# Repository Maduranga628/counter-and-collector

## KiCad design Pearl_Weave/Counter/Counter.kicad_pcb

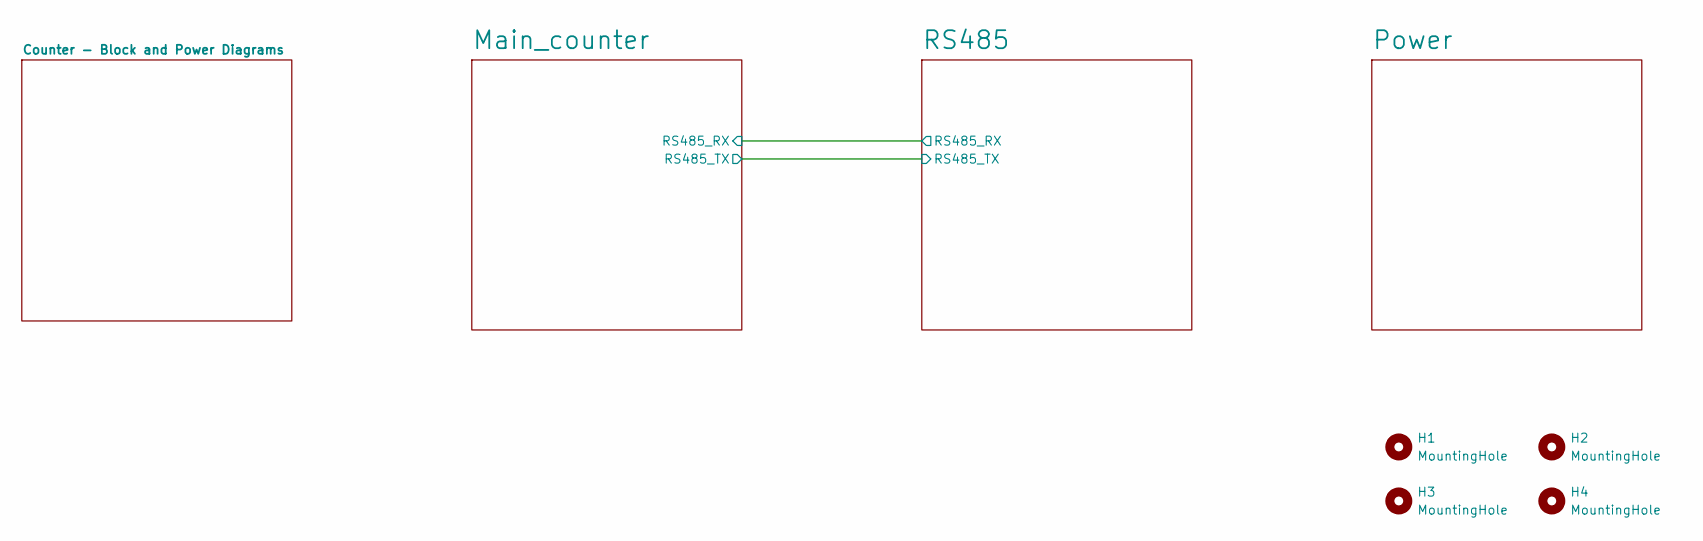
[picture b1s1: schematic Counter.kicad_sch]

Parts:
H1, H2, H3, H4: MountingHole; MountingHole_3.2mm_M3

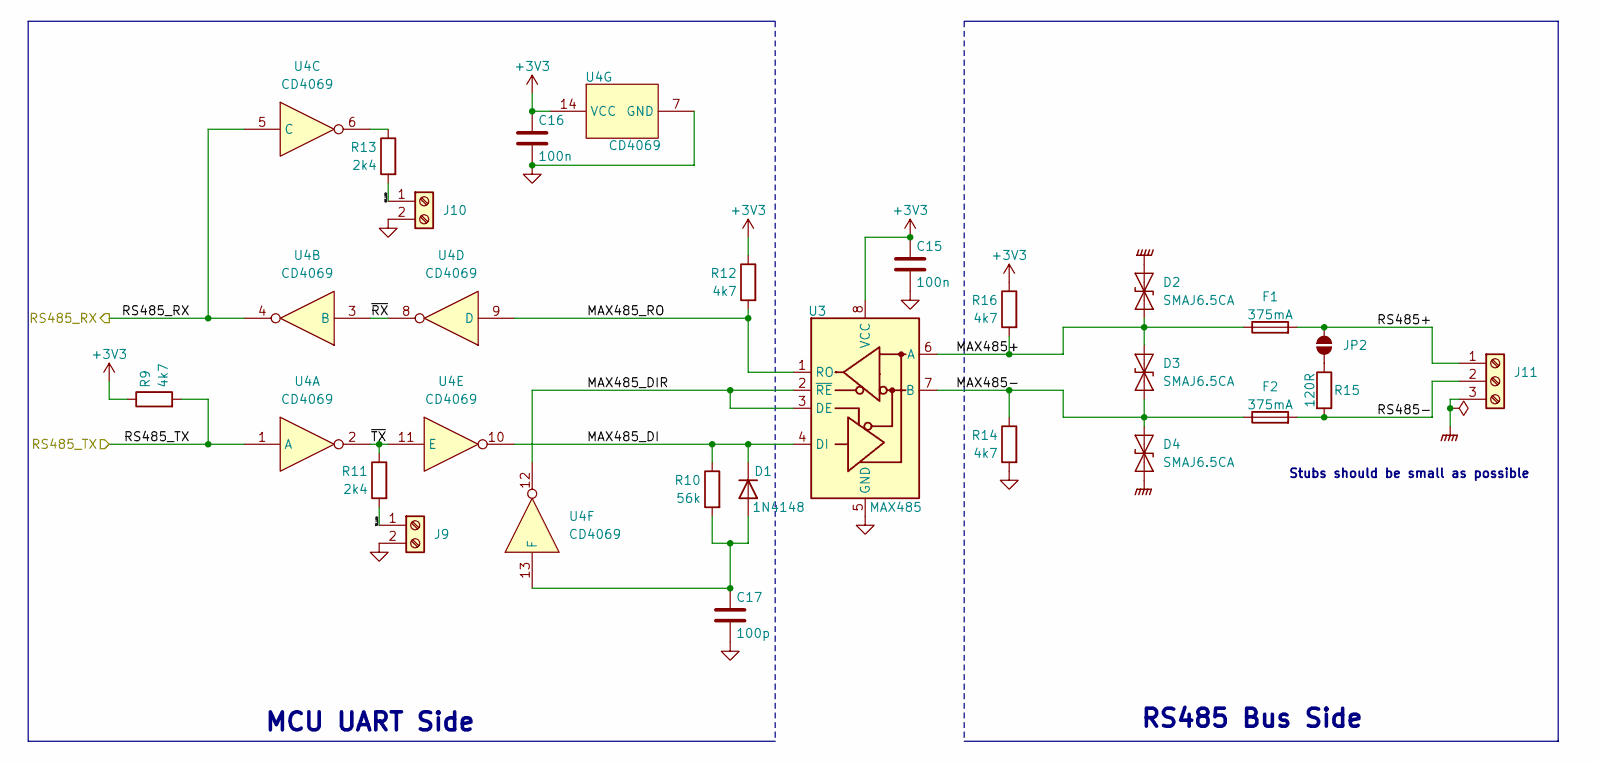
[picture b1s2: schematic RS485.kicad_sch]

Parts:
C15, C16: 100n; C_0603_1608Metric; Manufacturer Part Number CC0603MRX7R7BB104; LCSC Part Number C2172848
C17: 100p; C_0603_1608Metric; Manufacturer Part Number CC0603FRNPO9BN101; LCSC Part Number C513648
D1: 1N4148; D_SOD-523; Manufacturer Part Number 1N4148WT; LCSC Part Number C917006
D2, D3, D4: SMAJ6.5CA; D_SMA; Manufacturer Part Number SMAJ6.5CA; LCSC Part Number C54318614
F1, F2: 375mA; Fuse_1206_3216Metric; Manufacturer Part Number F12F0.375TH; LCSC Part Number C41398705
J9, J10: Screw_Terminal_01x02; TerminalBlock_Phoenix_MPT-0,5-2-2.54_1x02_P2.54mm_Horizontal
J11: Screw_Terminal_01x03; TerminalBlock_Phoenix_MPT-0,5-3-2.54_1x03_P2.54mm_Horizontal
JP2: SolderJumper_2_Open; SolderJumper-2_P1.3mm_Open_RoundedPad1.0x1.5mm
R9, R12, R14, R16: 4k7; R_0603_1608Metric; Manufacturer Part Number RC0603FR-074K7L; LCSC Part Number C99782
R10: 56k; R_0603_1608Metric; Manufacturer Part Number RC0603FR-0756KL; LCSC Part Number C114630
R11, R13: 2k4; R_0603_1608Metric; Manufacturer Part Number RC0603FR-072K4L; LCSC Part Number C114611
R15: 120R; R_0603_1608Metric; Manufacturer Part Number RC0603FR-07120RL; LCSC Part Number C114640
U3: MAX485; SOIC-8_3.9x4.9mm_P1.27mm; Manufacturer Part Number MAX485CSA+T-JSM; LCSC Part Number C18195057
U4: CD4069; SOIC-14_3.9x8.7mm_P1.27mm; Manufacturer Part Number CD4069; LCSC Part Number C3041279

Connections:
+3V3: C15.1, C16.1, R9.1, R12.1, R16.1, U3.8 (VCC), U4.14 (VCC); also elsewhere on the board
/Main_counter/RS485_RX: U4.4, U4.5 (C); also elsewhere on the board
/Main_counter/RS485_TX: R9.2, U4.1 (A); also elsewhere on the board
/RS485/MAX485+: D2.1 (A1), D3.2 (A2), F1.1, R16.2, U3.6 (A)
/RS485/MAX485-: D3.1 (A1), D4.2 (A2), F2.1, R14.1, U3.7 (B)
/RS485/MAX485_DI: D1.1 (K), R10.1, U3.4 (DI), U4.10
/RS485/MAX485_DIR: U3.2 (~RE), U3.3 (DE), U4.12
/RS485/MAX485_RO: R12.2, U3.1 (RO), U4.9 (D)
/RS485/RS485+: F1.2, J11.1, JP2.2 (B)
/RS485/RS485-: F2.2, J11.2, R15.2
/RS485/RX_LED: J10.1, R13.2
/RS485/TX_LED: J9.1, R11.2
/RS485/~RX: U4.3 (B), U4.8
/RS485/~TX: R11.1, U4.2, U4.11 (E)
GND: C15.2, C16.2, C17.2, J9.2, J10.2, R14.2, U3.5 (GND), U4.7 (GND); also elsewhere on the board
GNDPWR: D2.2 (A2), D4.1 (A1), J11.3
unnamed: C17.1, D1.2 (A), R10.2, U4.13 (F)
unnamed: JP2.1 (A), R15.1
unnamed: R13.1, U4.6

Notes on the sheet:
MCU UART Side
Stubs should be small as possible
RS485 Bus Side

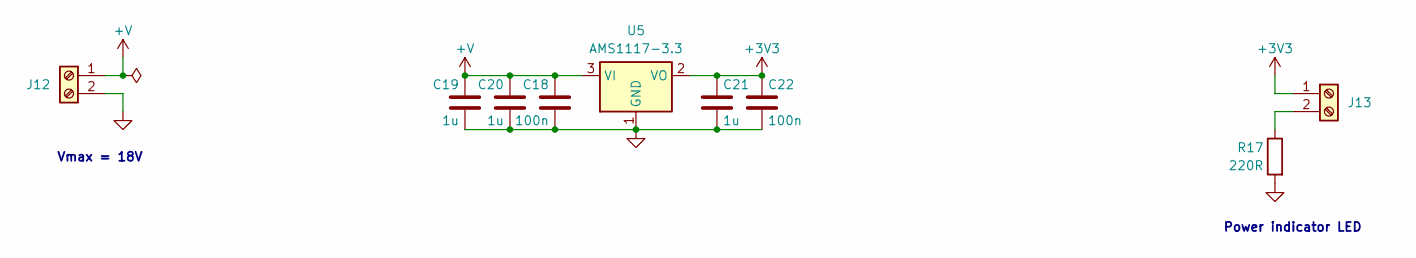
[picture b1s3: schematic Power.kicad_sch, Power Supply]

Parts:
C18, C22: 100n; C_0603_1608Metric; Manufacturer Part Number CC0603MRX7R7BB104; LCSC Part Number C2172848
C19, C20, C21: 1u; C_0603_1608Metric; Manufacturer Part Number CC0603KRX7R9BB105; LCSC Part Number C14664
J12, J13: Screw_Terminal_01x02; TerminalBlock_Phoenix_MPT-0,5-2-2.54_1x02_P2.54mm_Horizontal
R17: 220R; R_0603_1608Metric; Manufacturer Part Number RC0603JR-07220RL; LCSC Part Number C114683
U5: AMS1117-3.3; SOT-223-3_TabPin2; Manufacturer Part Number AMS1117-3.3(SOT-223); LCSC Part Number C5346136

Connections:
+3V3: C21.1, C22.1, J13.1, U5.2 (VO); also elsewhere on the board
+V: C18.1, C19.1, C20.1, J12.1, U5.3 (VI)
GND: C18.2, C19.2, C20.2, C21.2, C22.2, J12.2, R17.2, U5.1 (GND); also elsewhere on the board
unnamed: J13.2, R17.1

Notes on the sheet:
Power indicator LED
Vmax = 18V

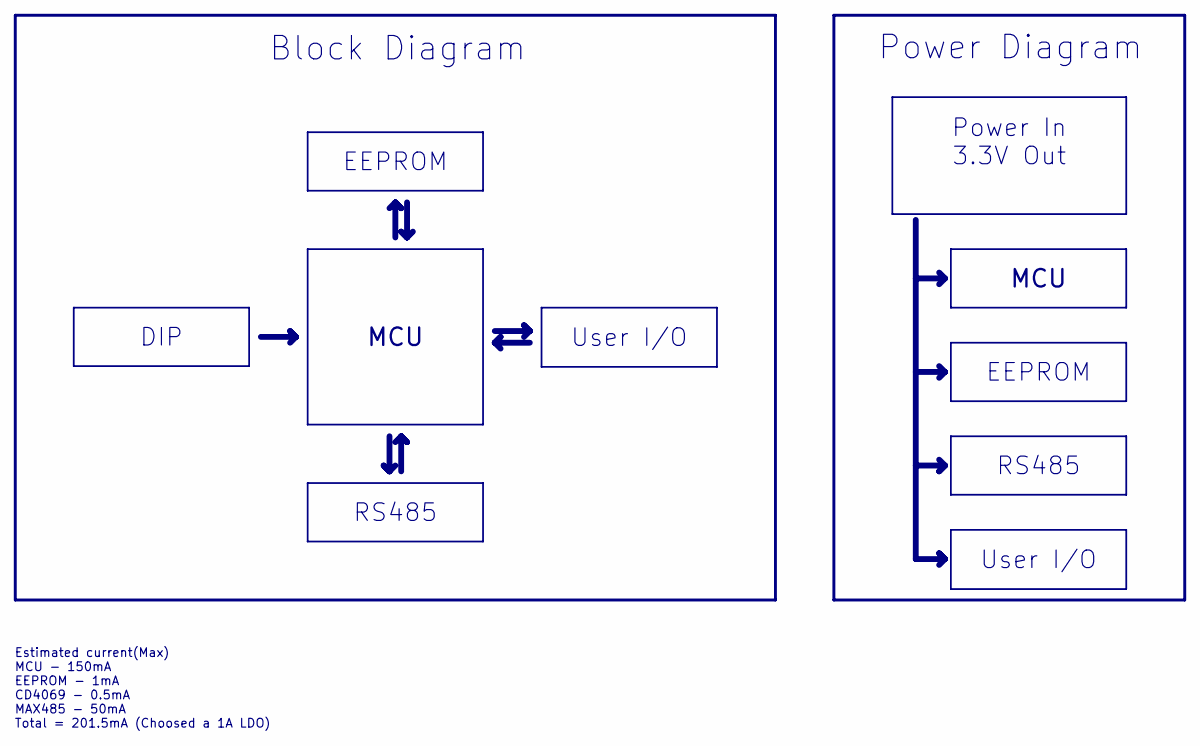
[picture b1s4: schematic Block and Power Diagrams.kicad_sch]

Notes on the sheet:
Block Diagram
Estimated current(Max) MCU - 150mA EEPROM - 1mA CD4069 - 0.5mA MAX485 - 50mA Total = 201.5mA (Choosed a 1A LDO)
Power Diagram
EEPROM
Power In 3.3V Out
MCU
User I/O
RS485
DIP

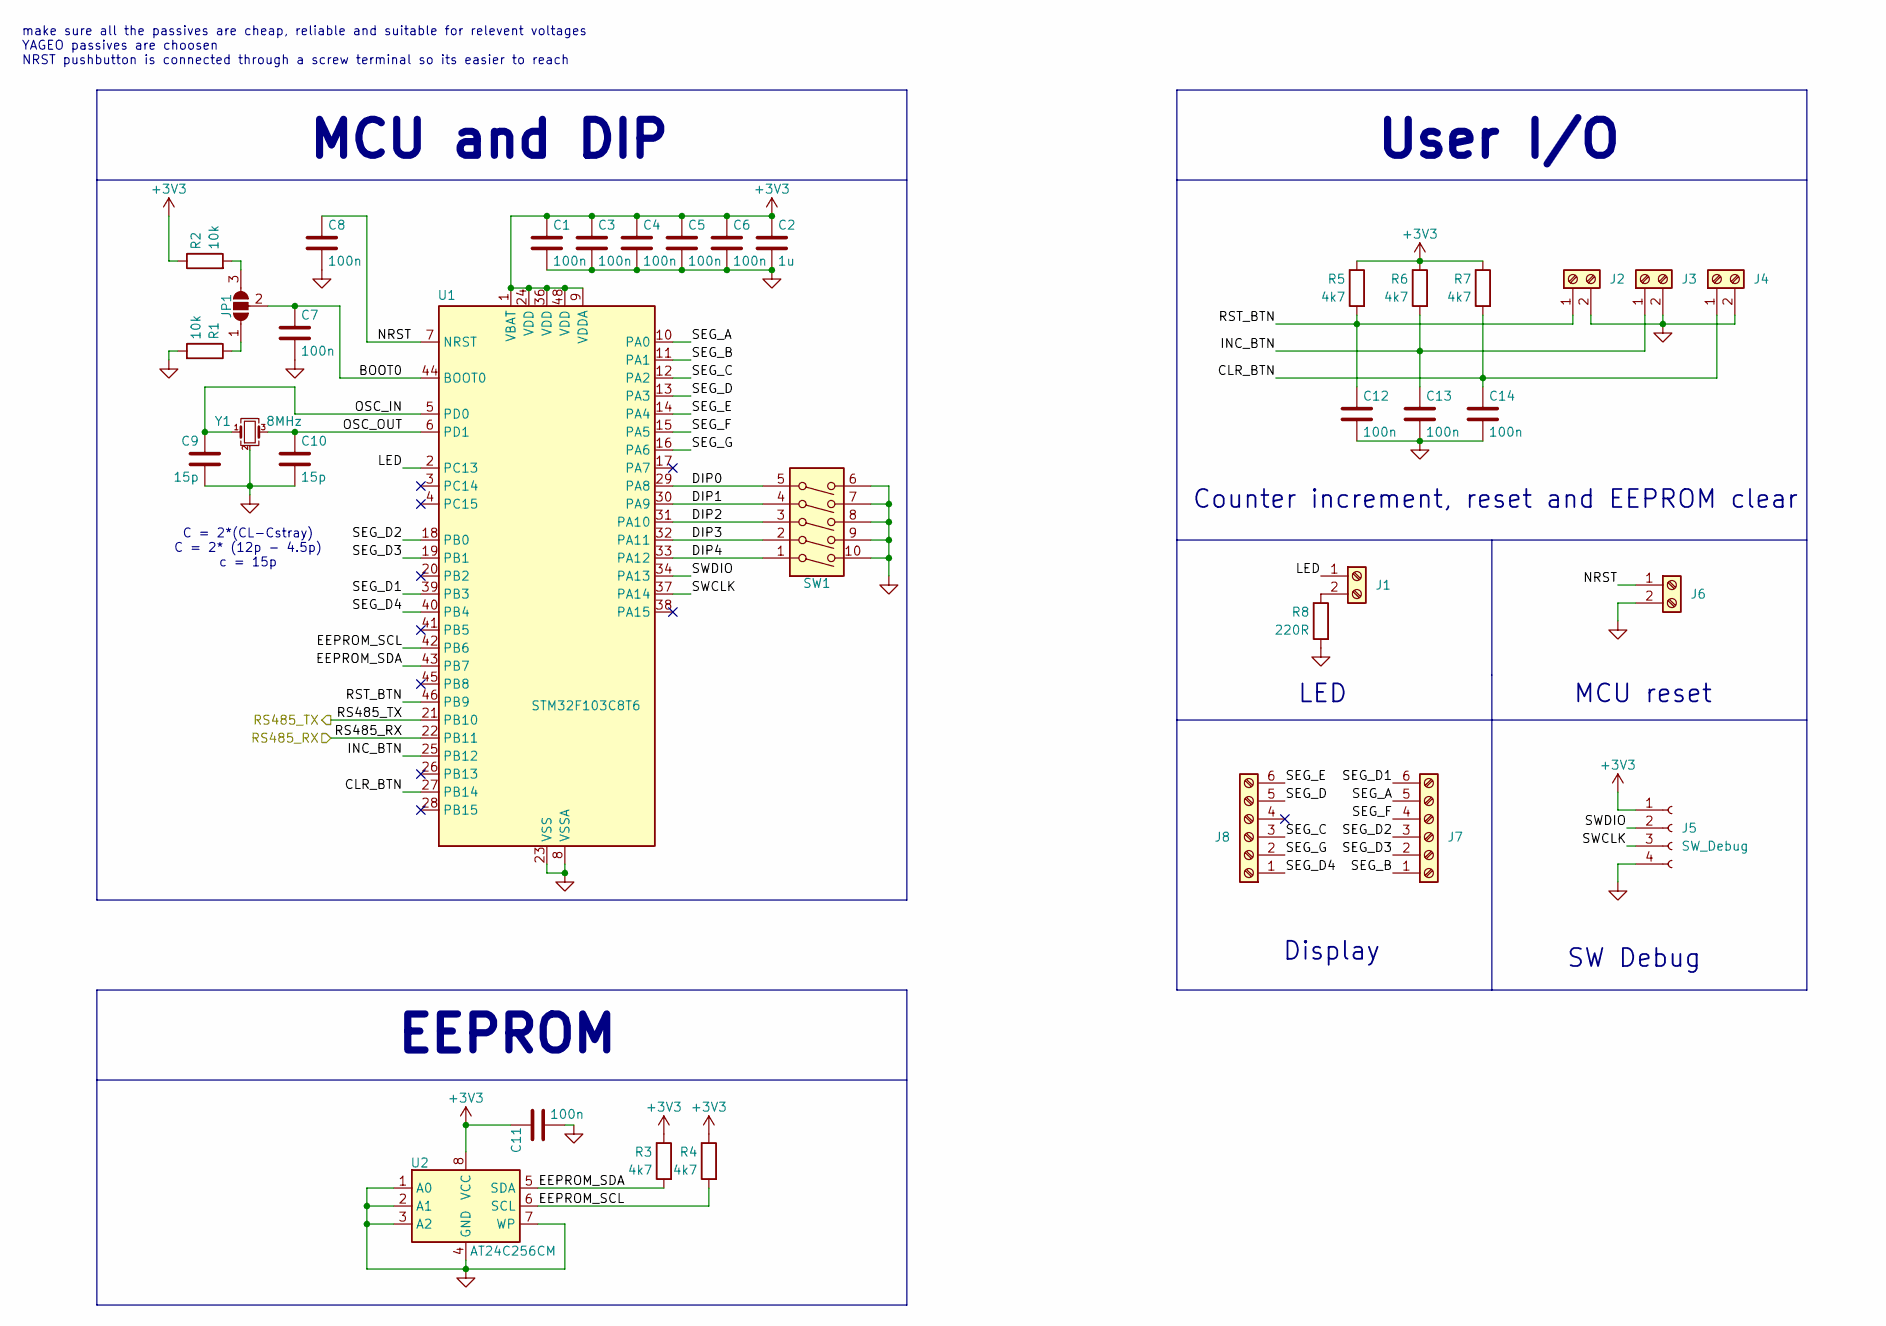
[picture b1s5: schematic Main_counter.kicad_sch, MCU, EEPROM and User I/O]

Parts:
C1, C3, C4, C5, C6, C7, C8, C11, C12, C13, C14: 100n; C_0603_1608Metric; Manufacturer Part Number CC0603MRX7R7BB104; LCSC Part Number C2172848
C2: 1u; C_0603_1608Metric; Manufacturer Part Number CC0603KRX7R9BB105; LCSC Part Number C14664
C9, C10: 15p; C_0603_1608Metric; Manufacturer Part Number CC0603FRNPO9BN150; LCSC Part Number C519483
J1, J2, J3, J4, J6: Screw_Terminal_01x02; TerminalBlock_Phoenix_MPT-0,5-2-2.54_1x02_P2.54mm_Horizontal
J5: SW_Debug; PinSocket_1x04_P2.54mm_Vertical
J7, J8: Screw_Terminal_01x06; TerminalBlock_Phoenix_MPT-0,5-6-2.54_1x06_P2.54mm_Horizontal
JP1: SolderJumper_3_Open; SolderJumper-3_P1.3mm_Open_RoundedPad1.0x1.5mm
R1, R2: 10k; R_0603_1608Metric; Manufacturer Part Number RC0603JR-0710KL; LCSC Part Number C99198
R3, R4, R5, R6, R7: 4k7; R_0603_1608Metric; Manufacturer Part Number RC0603FR-074K7L; LCSC Part Number C99782
R8: 220R; R_0603_1608Metric; Manufacturer Part Number RC0603JR-07220RL; LCSC Part Number C114683
SW1: SW_DIP_x05; SW_DIP_SPSTx05_Slide_9.78x14.88mm_W7.62mm_P2.54mm
U1: STM32F103C8T6; LQFP-48_7x7mm_P0.5mm
U2: AT24C256CM; SOP-8_3.76x4.96mm_P1.27mm; Manufacturer Part Number AT24C256CM/TR; LCSC Part Number C7432367
Y1: 8MHz; Crystal_SMD_3225-4Pin_3.2x2.5mm; Manufacturer Part Number SX32Y008000BC1T001; LCSC Part Number C20617233

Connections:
+3V3: C1.1, C2.1, C3.1, C4.1, C5.1, C6.1, C11.1, J5.1, R2.1, R3.1, R4.1, R5.1, R6.1, R7.1, U1.1 (VBAT), U1.9 (VDDA), U1.24 (VDD), U1.36 (VDD), U1.48 (VDD), U2.8 (VCC); also elsewhere on the board
/Main_counter/BOOT0: C7.1, JP1.2 (C), U1.44 (BOOT0)
/Main_counter/CLR_BTN: C14.1, J4.1, R7.2, U1.27 (PB14)
/Main_counter/DIP0: SW1.5, U1.29 (PA8)
/Main_counter/DIP1: SW1.4, U1.30 (PA9)
/Main_counter/DIP2: SW1.3, U1.31 (PA10)
/Main_counter/DIP3: SW1.2, U1.32 (PA11)
/Main_counter/DIP4: SW1.1, U1.33 (PA12)
/Main_counter/EEPROM_SCL: R4.2, U1.42 (PB6), U2.6 (SCL)
/Main_counter/EEPROM_SDA: R3.2, U1.43 (PB7), U2.5 (SDA)
/Main_counter/INC_BTN: C13.1, J3.1, R6.2, U1.25 (PB12)
/Main_counter/LED: J1.1, U1.2 (PC13)
/Main_counter/NRST: C8.1, J6.1, U1.7 (NRST)
/Main_counter/OSC_IN: C9.1, U1.5 (PD0), Y1.1
/Main_counter/OSC_OUT: C10.1, U1.6 (PD1), Y1.3
/Main_counter/RS485_RX: U1.22 (PB11); also elsewhere on the board
/Main_counter/RS485_TX: U1.21 (PB10); also elsewhere on the board
/Main_counter/RST_BTN: C12.1, J2.1, R5.2, U1.46 (PB9)
/Main_counter/SEG_A: J7.5, U1.10 (PA0)
/Main_counter/SEG_B: J7.1, U1.11 (PA1)
/Main_counter/SEG_C: J8.3, U1.12 (PA2)
/Main_counter/SEG_D: J8.5, U1.13 (PA3)
/Main_counter/SEG_D1: J7.6, U1.39 (PB3)
/Main_counter/SEG_D2: J7.3, U1.18 (PB0)
/Main_counter/SEG_D3: J7.2, U1.19 (PB1)
/Main_counter/SEG_D4: J8.1, U1.40 (PB4)
/Main_counter/SEG_E: J8.6, U1.14 (PA4)
/Main_counter/SEG_F: J7.4, U1.15 (PA5)
/Main_counter/SEG_G: J8.2, U1.16 (PA6)
/Main_counter/SWCLK: J5.3, U1.37 (PA14)
/Main_counter/SWDIO: J5.2, U1.34 (PA13)
GND: C1.2, C2.2, C3.2, C4.2, C5.2, C6.2, C7.2, C8.2, C9.2, C10.2, C11.2, C12.2, C13.2, C14.2, J2.2, J3.2, J4.2, J5.4, J6.2, R1.2, R8.2, SW1.6, SW1.7, SW1.8, SW1.9, SW1.10, U1.8 (VSSA), U1.23 (VSS), U1.35 (VSS), U1.47 (VSS), U2.1 (A0), U2.2 (A1), U2.3 (A2), U2.4 (GND), U2.7 (WP), Y1.2 (G), Y1.4 (G); also elsewhere on the board
unnamed: J1.2, R8.1
unnamed: JP1.1 (A), R1.1
unnamed: JP1.3 (B), R2.2

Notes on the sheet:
User I/O
Counter increment, reset and EEPROM clear
C = 2*(CL-Cstray) C = 2* (12p - 4.5p) c = 15p
SW Debug
Display
MCU and DIP
EEPROM
make sure all the passives are cheap, reliable and suitable for relevent voltages YAGEO passives are choosen NRST pushbutton is connected through a screw terminal so its easier to reach
LED
MCU reset

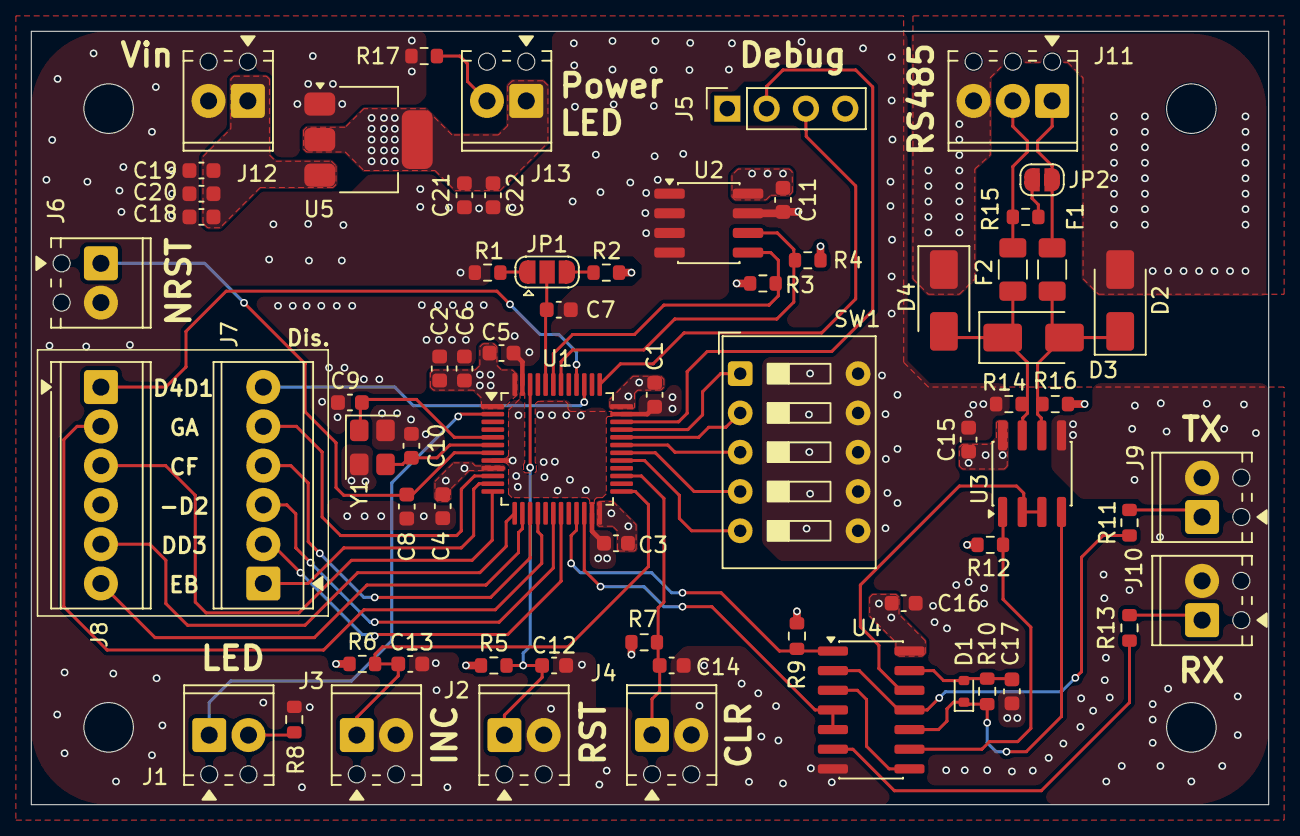
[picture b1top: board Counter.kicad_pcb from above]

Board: 4 copper layers, 80.0 x 50.0 mm, 71 parts (0 on the bottom side), 52 nets.

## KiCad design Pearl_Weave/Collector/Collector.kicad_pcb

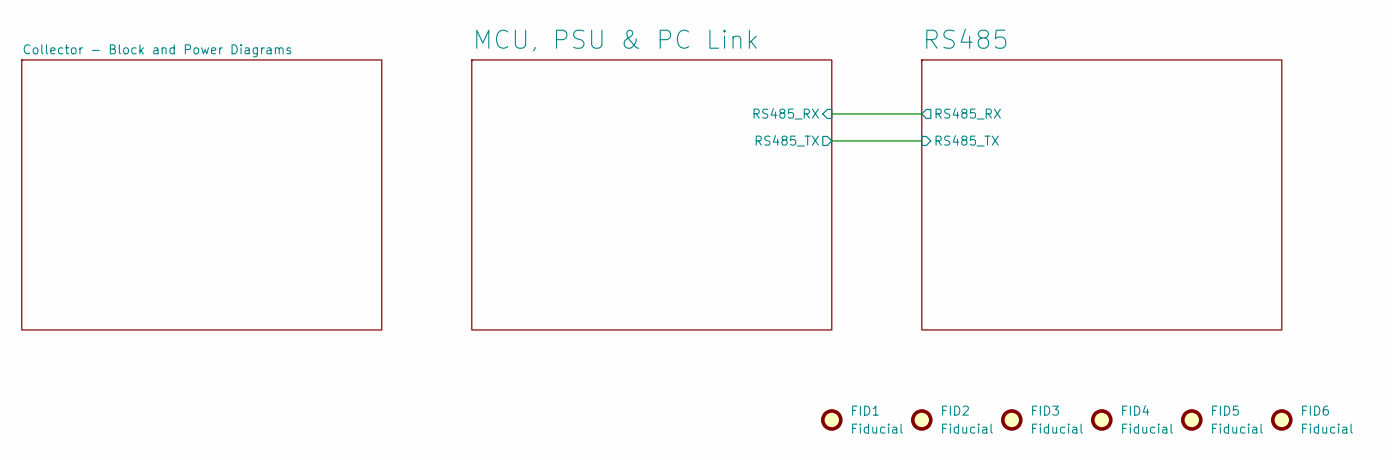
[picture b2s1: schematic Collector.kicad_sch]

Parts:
FID1, FID2, FID3, FID4, FID5, FID6: Fiducial; Fiducial_0.5mm_Mask1mm

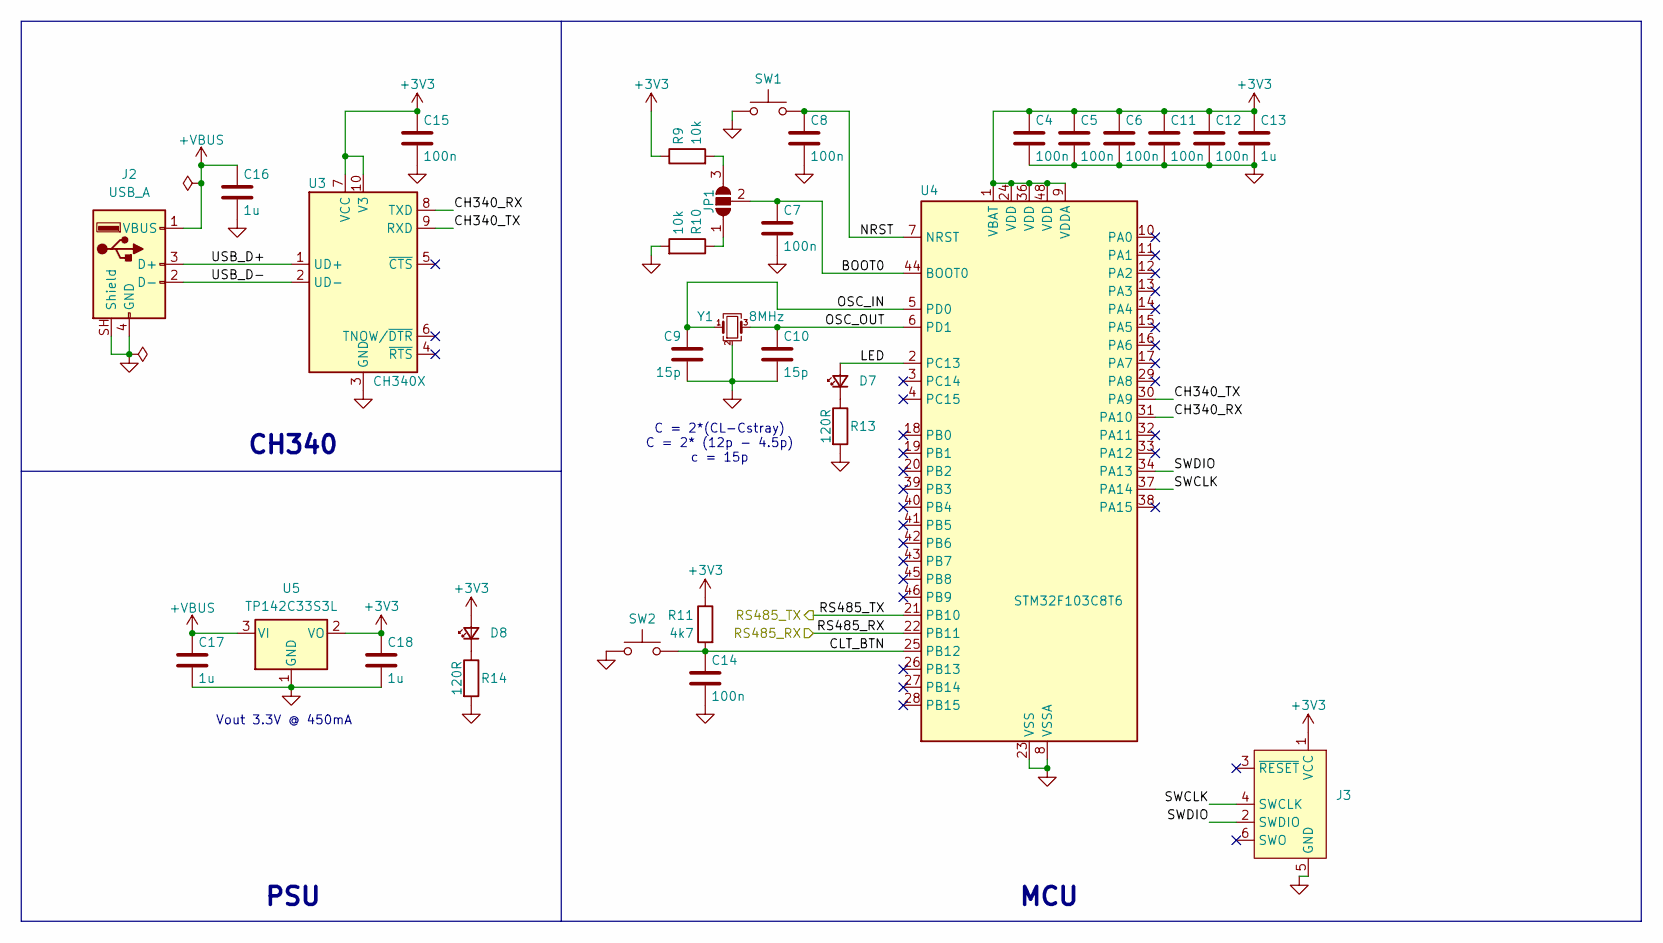
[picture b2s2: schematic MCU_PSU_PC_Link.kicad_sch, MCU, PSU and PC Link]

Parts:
C4, C5, C6, C7, C8, C11, C12, C14, C15: 100n; C_0603_1608Metric; Manufacturer Part Number CC0603MRX7R7BB104; LCSC Part Number C2172848
C9, C10: 15p; C_0603_1608Metric; Manufacturer Part Number CC0603FRNPO9BN150; LCSC Part Number C519483
C13, C16, C17, C18: 1u; C_0603_1608Metric; Manufacturer Part Number CC0603KRX7R9BB105; LCSC Part Number C14664
D7: LED_Small; LED_0603_1608Metric; Manufacturer Part Number YLED0603G; LCSC Part Number C19273151
D8: LED_Small; LED_0603_1608Metric; Manufacturer Part Number YLED0603R; LCSC Part Number C19171390
J2: USB_A; USB_A_CNCTech_1001-011-01101_Horizontal
J3: Conn_ARM_SWD_TagConnect_TC2030; Tag-Connect_TC2030-IDC-FP_2x03_P1.27mm_Vertical
JP1: SolderJumper_3_Open; SolderJumper-3_P1.3mm_Open_RoundedPad1.0x1.5mm
R9, R10: 10k; R_0603_1608Metric; Manufacturer Part Number RC0603JR-0710KL; LCSC Part Number C99198
R11: 4k7; R_0603_1608Metric; Manufacturer Part Number RC0603FR-074K7L; LCSC Part Number C99782
R13, R14: 120R; R_0603_1608Metric; Manufacturer Part Number RC0603FR-07120RL; LCSC Part Number C114640
SW1: SW_Push; SW_DIP_SPSTx01_Slide_6.7x4.1mm_W6.73mm_P2.54mm_LowProfile_J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; Manufacturer Part Number R4A25211L; LCSC Part Number C49393629
SW2: SW_Push; SW_Push_1P1T_NO_CK_KSC9xxG
U3: CH340X; MSOP-10_3x3mm_P0.5mm; Manufacturer Part Number CH340X; LCSC Part Number C3035748
U4: STM32F103C8T6; LQFP-48_7x7mm_P0.5mm
U5: TP142C33S3L; SOT-23; Manufacturer Part Number TP142C33S3L; LCSC Part Number C3021129
Y1: 8MHz; Crystal_SMD_3225-4Pin_3.2x2.5mm; Manufacturer Part Number SX32Y008000BC1T001; LCSC Part Number C20617233

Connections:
+3V3: C4.1, C5.1, C6.1, C11.1, C12.1, C13.1, C15.1, C18.1, D8.2 (A), J3.1 (VCC), R9.1, R11.1, U3.7 (VCC), U3.10 (V3), U4.1 (VBAT), U4.9 (VDDA), U4.24 (VDD), U4.36 (VDD), U4.48 (VDD), U5.2 (VO); also elsewhere on the board
+VBUS: C16.1, C17.1, J2.1 (VBUS), U5.3 (VI)
/MCU, PSU & PC Link/BOOT0: C7.1, JP1.2 (C), U4.44 (BOOT0)
/MCU, PSU & PC Link/CH340_RX: U3.8 (TXD), U4.31 (PA10)
/MCU, PSU & PC Link/CH340_TX: U3.9 (RXD), U4.30 (PA9)
/MCU, PSU & PC Link/CLT_BTN: C14.1, R11.2, SW2.2, U4.25 (PB12)
/MCU, PSU & PC Link/LED: D7.2 (A), U4.2 (PC13)
/MCU, PSU & PC Link/NRST: C8.1, SW1.2, U4.7 (NRST)
/MCU, PSU & PC Link/OSC_IN: C9.1, U4.5 (PD0), Y1.1
/MCU, PSU & PC Link/OSC_OUT: C10.1, U4.6 (PD1), Y1.3
/MCU, PSU & PC Link/RS485_RX: U4.22 (PB11); also elsewhere on the board
/MCU, PSU & PC Link/RS485_TX: U4.21 (PB10); also elsewhere on the board
/MCU, PSU & PC Link/SWCLK: J3.4 (SWCLK), U4.37 (PA14)
/MCU, PSU & PC Link/SWDIO: J3.2 (SWDIO), U4.34 (PA13)
/MCU, PSU & PC Link/USB_D+: J2.3 (D+), U3.1 (UD+)
/MCU, PSU & PC Link/USB_D-: J2.2 (D-), U3.2 (UD-)
GND: C4.2, C5.2, C6.2, C7.2, C8.2, C9.2, C10.2, C11.2, C12.2, C13.2, C14.2, C15.2, C16.2, C17.2, C18.2, J2.4 (GND), J2.SH (Shield), J3.5 (GND), R10.2, R13.2, R14.2, SW1.1, SW2.1, U3.3 (GND), U4.8 (VSSA), U4.23 (VSS), U4.35 (VSS), U4.47 (VSS), U5.1 (GND), Y1.2 (G), Y1.4 (G); also elsewhere on the board
unnamed: D7.1 (K), R13.1
unnamed: D8.1 (K), R14.1
unnamed: JP1.1 (A), R10.1
unnamed: JP1.3 (B), R9.2

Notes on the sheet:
PSU
CH340
Vout 3.3V @ 450mA
MCU
C = 2*(CL-Cstray) C = 2* (12p - 4.5p) c = 15p

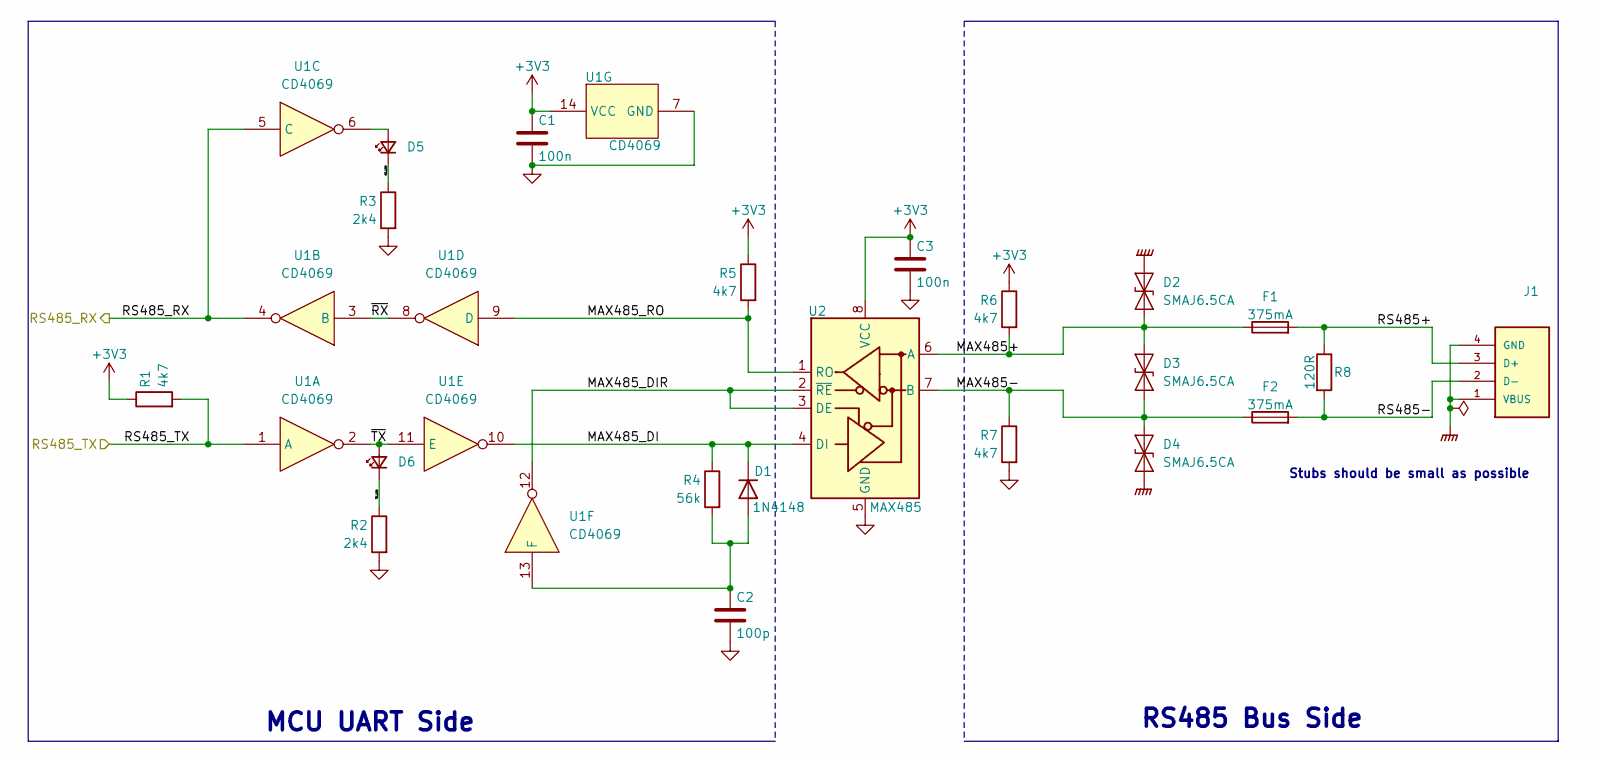
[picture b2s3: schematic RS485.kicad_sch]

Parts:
C1, C3: 100n; C_0603_1608Metric; Manufacturer Part Number CC0603MRX7R7BB104; LCSC Part Number C2172848
C2: 100p; C_0603_1608Metric; Manufacturer Part Number CC0603FRNPO9BN101; LCSC Part Number C513648
D1: 1N4148; D_SOD-523; Manufacturer Part Number 1N4148WT; LCSC Part Number C917006
D2, D3, D4: SMAJ6.5CA; D_SMA; Manufacturer Part Number SMAJ6.5CA; LCSC Part Number C54318614
D5, D6: LED_Small; LED_0603_1608Metric; Manufacturer Part Number YLED0603R; LCSC Part Number C19171390
F1, F2: 375mA; Fuse_1206_3216Metric; Manufacturer Part Number F12F0.375TH; LCSC Part Number C41398705
J1: USB-A1HSW6; OST_USB-A1HSW6; PARTREV A
R1, R5, R6, R7: 4k7; R_0603_1608Metric; Manufacturer Part Number RC0603FR-074K7L; LCSC Part Number C99782
R2, R3: 2k4; R_0603_1608Metric; Manufacturer Part Number RC0603FR-072K4L; LCSC Part Number C114611
R4: 56k; R_0603_1608Metric; Manufacturer Part Number RC0603FR-0756KL; LCSC Part Number C114630
R8: 120R; R_0603_1608Metric; Manufacturer Part Number RC0603FR-07120RL; LCSC Part Number C114640
U1: CD4069; SOIC-14_3.9x8.7mm_P1.27mm; Manufacturer Part Number CD4069; LCSC Part Number C3041279
U2: MAX485; SOIC-8_3.9x4.9mm_P1.27mm; Manufacturer Part Number MAX485CSA+T-JSM; LCSC Part Number C18195057

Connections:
+3V3: C1.1, C3.1, R1.1, R5.1, R6.1, U1.14 (VCC), U2.8 (VCC); also elsewhere on the board
/MCU, PSU & PC Link/RS485_RX: U1.4, U1.5 (C); also elsewhere on the board
/MCU, PSU & PC Link/RS485_TX: R1.2, U1.1 (A); also elsewhere on the board
/RS485/MAX485+: D2.1 (A1), D3.2 (A2), F1.1, R6.2, U2.6 (A)
/RS485/MAX485-: D3.1 (A1), D4.2 (A2), F2.1, R7.1, U2.7 (B)
/RS485/MAX485_DI: D1.1 (K), R4.1, U1.10, U2.4 (DI)
/RS485/MAX485_DIR: U1.12, U2.2 (~RE), U2.3 (DE)
/RS485/MAX485_RO: R5.2, U1.9 (D), U2.1 (RO)
/RS485/RS485+: F1.2, J1.3 (D+), R8.1
/RS485/RS485-: F2.2, J1.2 (D-), R8.2
/RS485/RX_LED: D5.1 (K), R3.1
/RS485/TX_LED: D6.1 (K), R2.1
/RS485/~RX: U1.3 (B), U1.8
/RS485/~TX: D6.2 (A), U1.2, U1.11 (E)
GND: C1.2, C2.2, C3.2, R2.2, R3.2, R7.2, U1.7 (GND), U2.5 (GND); also elsewhere on the board
GNDPWR: D2.2 (A2), D4.1 (A1), J1.1 (VBUS), J1.4 (GND)
unnamed: C2.1, D1.2 (A), R4.2, U1.13 (F)
unnamed: D5.2 (A), U1.6

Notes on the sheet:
MCU UART Side
Stubs should be small as possible
RS485 Bus Side

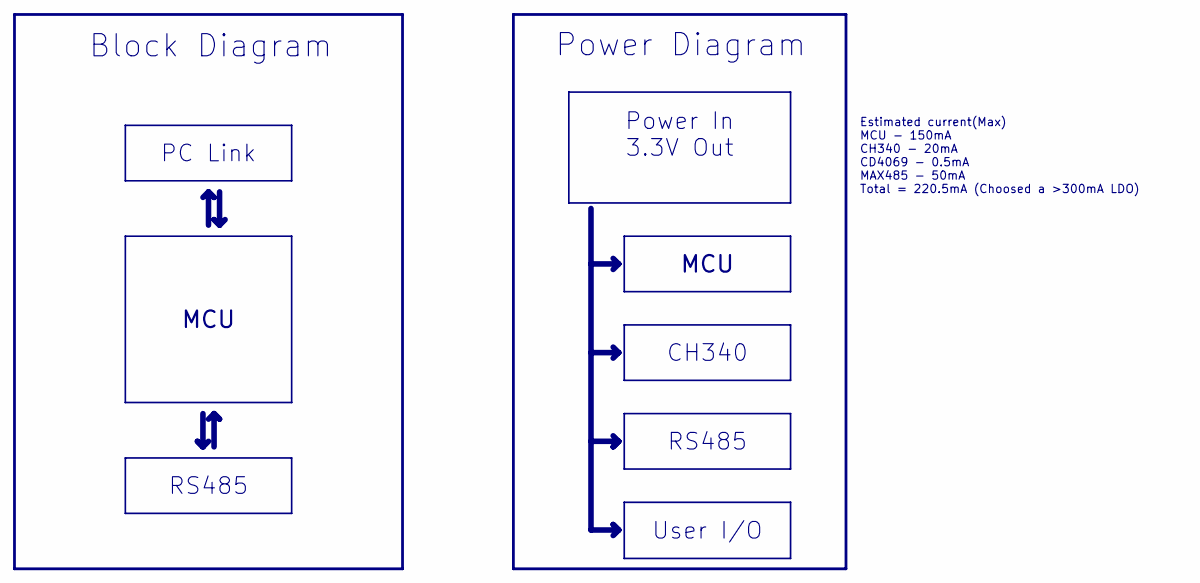
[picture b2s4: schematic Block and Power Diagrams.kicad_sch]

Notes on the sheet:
Power Diagram
Block Diagram
Estimated current(Max) MCU - 150mA CH340 - 20mA CD4069 - 0.5mA MAX485 - 50mA Total = 220.5mA (Choosed a >300mA LDO)
User I/O
RS485
MCU
CH340
Power In 3.3V Out
PC Link

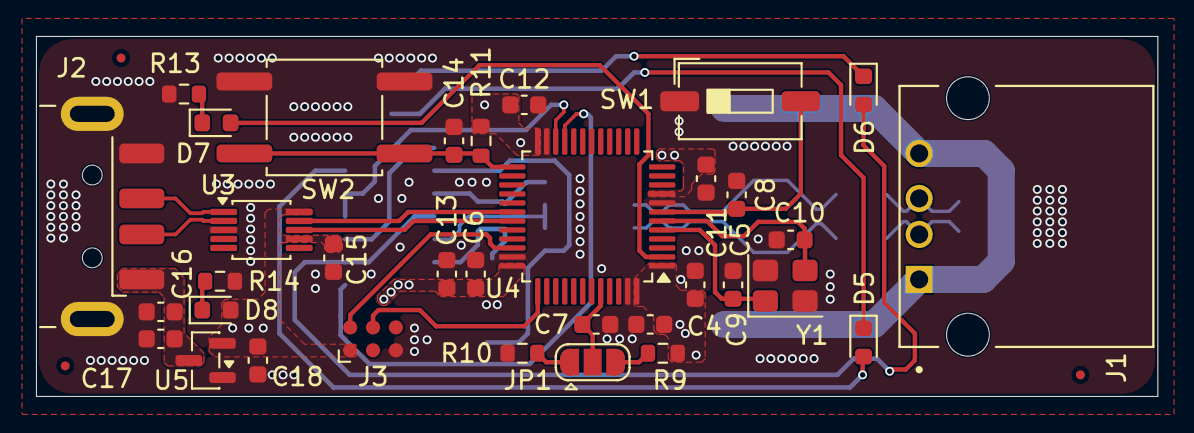
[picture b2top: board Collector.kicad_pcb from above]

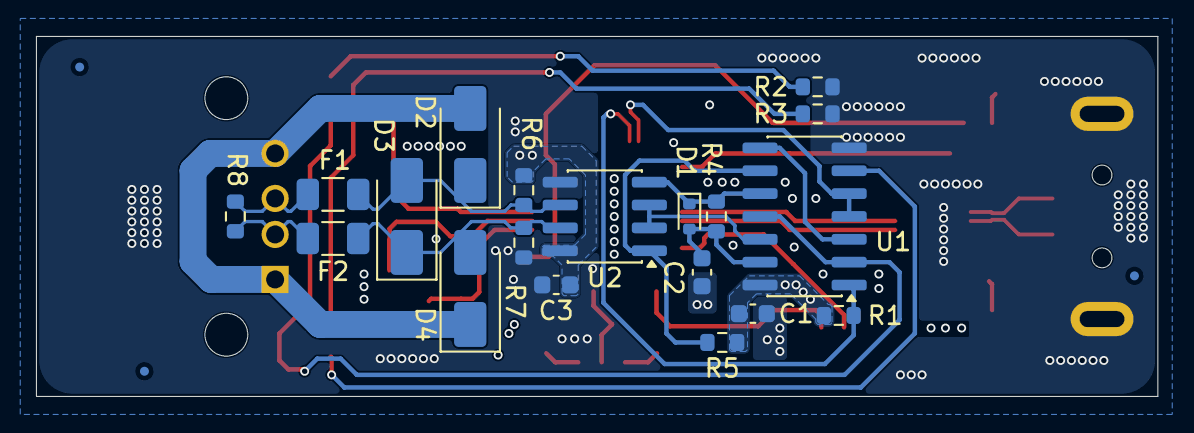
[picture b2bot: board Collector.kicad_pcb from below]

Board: 4 copper layers, 62.3 x 20.0 mm, 59 parts (22 on the bottom side), 35 nets.

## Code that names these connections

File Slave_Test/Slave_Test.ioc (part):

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Mcu.Name=STM32F103C(8-B)Tx
Mcu.Package=LQFP48
Mcu.UserName=STM32F103C8Tx
PA0-WKUP.GPIOParameters=GPIO_Label
PA0-WKUP.GPIO_Label=SEG_A
PA0-WKUP.Signal=GPIO_Output
PA1.GPIOParameters=GPIO_Label
PA1.GPIO_Label=SEG_B
PA1.Signal=GPIO_Output
PA10.GPIOParameters=GPIO_PuPd,GPIO_Label
PA10.GPIO_Label=DIP2
PA10.GPIO_PuPd=GPIO_PULLUP
PA10.Signal=GPIO_Input
PA11.GPIOParameters=GPIO_PuPd,GPIO_Label
PA11.GPIO_Label=DIP3
PA11.GPIO_PuPd=GPIO_PULLUP
PA11.Signal=GPIO_Input
PA12.GPIOParameters=GPIO_PuPd,GPIO_Label
PA12.GPIO_Label=DIP4
PA12.GPIO_PuPd=GPIO_PULLUP
PA12.Signal=GPIO_Input
PA13.Mode=Serial_Wire
PA13.Signal=SYS_JTMS-SWDIO
PA14.Mode=Serial_Wire
PA14.Signal=SYS_JTCK-SWCLK
PA2.GPIOParameters=GPIO_Label
PA2.GPIO_Label=SEG_C
PA2.Signal=GPIO_Output
PA3.GPIOParameters=GPIO_Label
PA3.GPIO_Label=SEG_D
PA3.Signal=GPIO_Output
PA4.GPIOParameters=GPIO_Label
PA4.GPIO_Label=SEG_E
PA4.Signal=GPIO_Output
PA5.GPIOParameters=GPIO_Label
PA5.GPIO_Label=SEG_F
PA5.Signal=GPIO_Output
PA6.GPIOParameters=GPIO_Label
PA6.GPIO_Label=SEG_G
PA6.Signal=GPIO_Output
PA8.GPIOParameters=GPIO_PuPd,GPIO_Label
PA8.GPIO_Label=DIP0
PA8.GPIO_PuPd=GPIO_PULLUP
PA8.Signal=GPIO_Input
PA9.GPIOParameters=GPIO_PuPd,GPIO_Label
PA9.GPIO_Label=DIP1
PA9.GPIO_PuPd=GPIO_PULLUP
PA9.Signal=GPIO_Input
PB0.GPIOParameters=GPIO_Label
PB0.GPIO_Label=SEG_D2
PB0.Signal=GPIO_Output
PB1.GPIOParameters=GPIO_Label
PB1.GPIO_Label=SEG_D3
PB1.Signal=GPIO_Output
PB10.Mode=Asynchronous
PB10.Signal=USART3_TX
PB11.Mode=Asynchronous
PB11.Signal=USART3_RX
PB12.GPIOParameters=GPIO_Label
PB12.GPIO_Label=INC_BTN
PB12.Signal=GPXTI12
PB14.GPIOParameters=GPIO_Label,GPIO_ModeDefaultEXTI
PB14.GPIO_Label=CLR_BTN
PB14.GPIO_ModeDefaultEXTI=GPIO_MODE_IT_RISING
PB14.Signal=GPXTI14
PB3.GPIOParameters=GPIO_Label
PB3.GPIO_Label=SEG_D1
PB3.Signal=GPIO_Output
PB4.GPIOParameters=GPIO_Label
PB4.GPIO_Label=SEG_D4
PB4.Signal=GPIO_Output
PB6.Mode=I2C
PB6.Signal=I2C1_SCL
PB7.Mode=I2C
PB7.Signal=I2C1_SDA
PB9.GPIOParameters=GPIO_Label
PB9.GPIO_Label=RST_BTN
PB9.Signal=GPXTI9
PC13-TAMPER-RTC.GPIOParameters=PinState,GPIO_Label
PC13-TAMPER-RTC.GPIO_Label=LED
PC13-TAMPER-RTC.PinState=GPIO_PIN_SET
PC13-TAMPER-RTC.Signal=GPIO_Output
PD0-OSC_IN.Mode=HSE-External-Oscillator
PD0-OSC_IN.Signal=RCC_OSC_IN
PD1-OSC_OUT.Mode=HSE-External-Oscillator
PD1-OSC_OUT.Signal=RCC_OSC_OUT
RCC.SYSCLKFreq_VALUE=72000000
RCC.SYSCLKSource=RCC_SYSCLKSOURCE_PLLCLK
board=custom

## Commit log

2026-06-08 firmware for the counter and colllector
2026-06-08 hardaware
2026-06-08 hardware files
